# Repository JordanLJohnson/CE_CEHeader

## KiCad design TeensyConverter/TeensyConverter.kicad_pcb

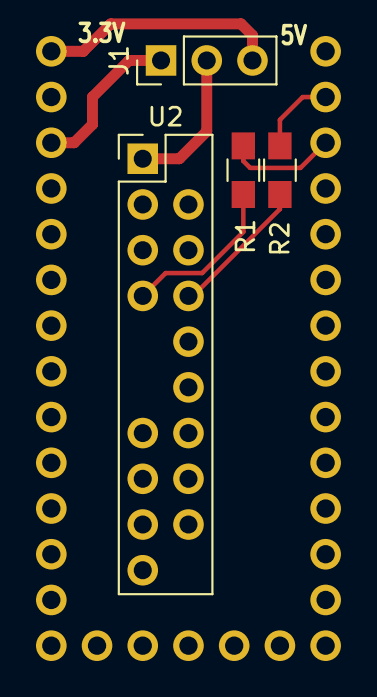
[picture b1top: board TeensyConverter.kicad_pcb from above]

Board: 2 copper layers, 5 parts (1 on the bottom side), 18 nets.

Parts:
J1: Conn_01x03; Pin_Header_Straight_1x03_Pitch2.54mm
R1, R2: R; R_0805_HandSoldering
U1: Teensy-3.2; Teensy-32
U2: CE_Header

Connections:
/3.3V: J1.1, U1.24, U2.12
/5V: J1.3, U1.26
/AIO0: U1.14, U2.15
/AIO1: U1.15, U2.16
/AIO2: U1.16, U2.17
/AIO3: U1.17, U2.18
/DEVICE_RX: R1.1, U2.7
/DEVICE_TX: R2.2, U2.8
/GND: U1.27, U1.30, U2.10, U2.19
/I2C_SCLK: U1.19, U2.13
/I2C_SDAT: U1.18, U2.14
/SPI_CLK: U1.13, U2.5
/SPI_CS: U1.10, U2.6
/SPI_MISO: U1.12, U2.4
/SPI_MOSI: U1.11, U2.3
/TEENSY_RX: R2.1, U1.0
/TEENSY_TX: R1.2, U1.1
unnamed: J1.2, U2.1

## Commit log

2018-05-06 Added gitignore
2018-05-06 Created CE Header schematic
2018-05-06 Created CE Header footprint
2018-05-26 Added CE_Header to schematic
2018-05-26 Added TeensyConverter project
2018-05-26 Moved CE_Header implementation into its own folder
2018-05-26 Connected Teensy to CE Header
2018-05-26 Associated TeensyConverter to components
2018-06-07 Flipped Teensy schematic and started netlist placement
